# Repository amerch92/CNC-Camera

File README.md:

# CNC Camera
 This is to make a Raspberry Pi Based Overhead Camera

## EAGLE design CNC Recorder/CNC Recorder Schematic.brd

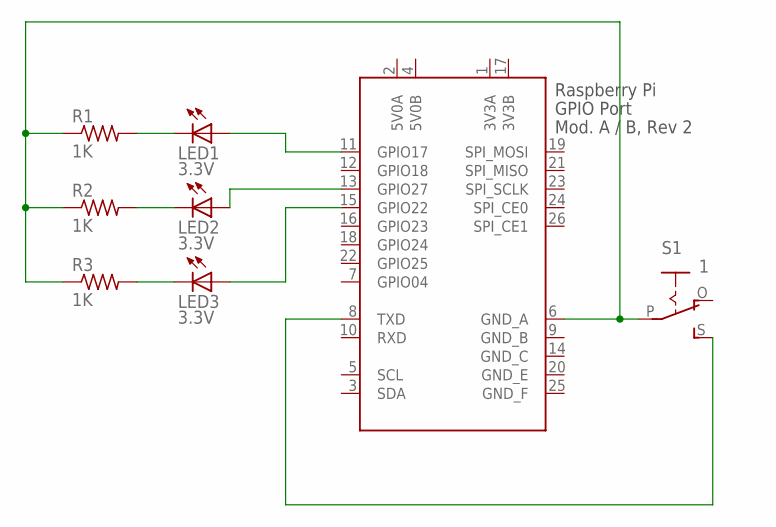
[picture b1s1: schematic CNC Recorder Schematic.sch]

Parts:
LED1, LED2, LED3: 3.3V; LED5MM
R1, R2, R3: 1K; 0207/10
S1: 1; EG1218
X1: RASPI_GPIO_AB#_PIN; RASPI_GPIO_AB_PIN

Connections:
3V3A: X1.1 (3V3A)
3V3B: X1.17 (3V3B)
5V0A: X1.2 (5V0A)
5V0B: X1.4 (5V0B)
GND_B: X1.9 (GND_B)
GND_C: X1.14 (GND_C)
GND_E: X1.20 (GND_E)
GND_F: X1.25 (GND_F)
unnamed: LED1.A, X1.11 (GPIO17)
unnamed: S1.S, X1.8 (TXD)
unnamed: LED2.A, X1.13 (GPIO27)
unnamed: LED3.A, X1.15 (GPIO22)
unnamed: LED1.K (C), R1.2
unnamed: LED2.K (C), R2.2
unnamed: LED3.K (C), R3.2
unnamed: R1.1, R2.1, R3.1, S1.P, X1.6 (GND_A)

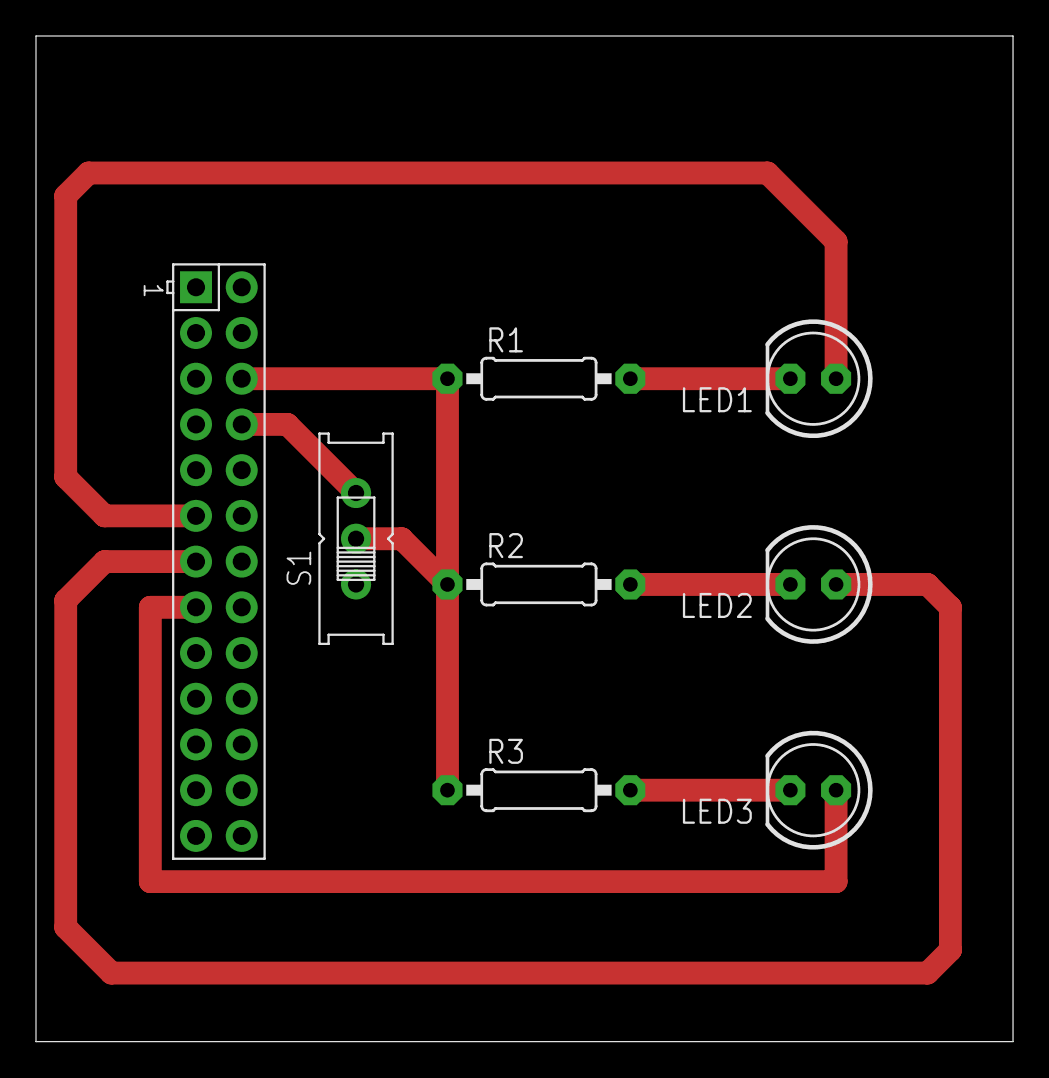
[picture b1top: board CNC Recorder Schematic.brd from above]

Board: 2 copper layers, 54.3 x 55.9 mm, 8 parts (0 on the bottom side), 8 nets.

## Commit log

2021-01-28 Init
2021-01-28 Python script
